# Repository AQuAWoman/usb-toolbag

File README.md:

# usb-toolbag
A versatile USB test kit based around the RP2040 chipset. Includes a pad for 8 bit ONFI standard chips.

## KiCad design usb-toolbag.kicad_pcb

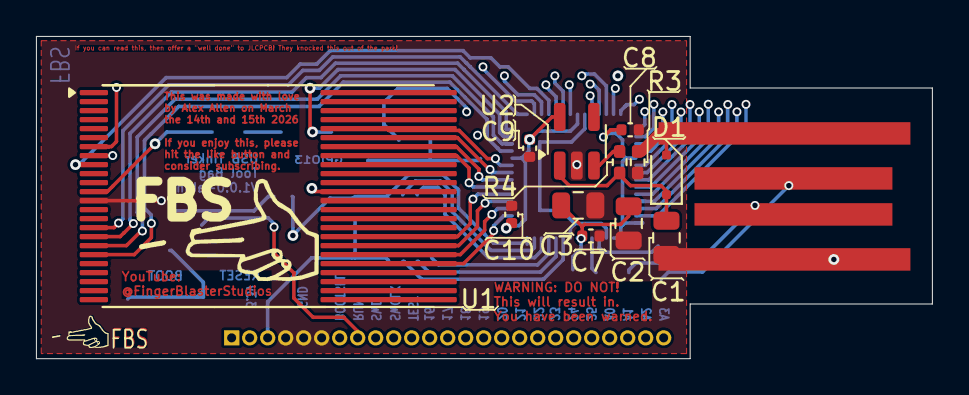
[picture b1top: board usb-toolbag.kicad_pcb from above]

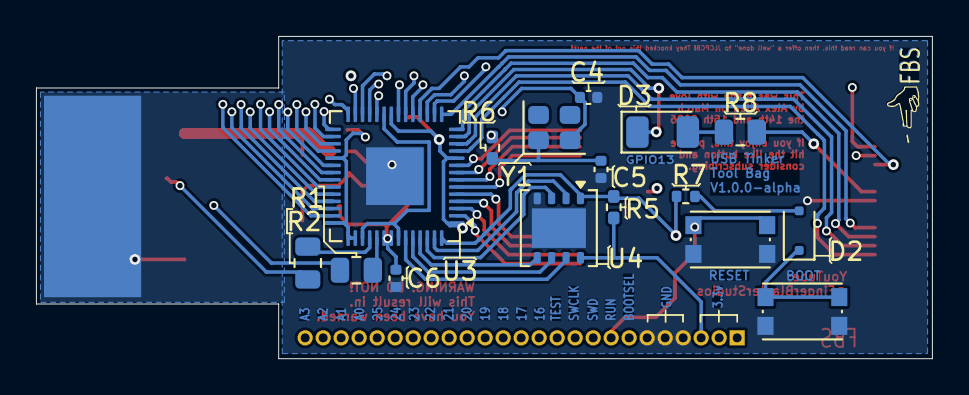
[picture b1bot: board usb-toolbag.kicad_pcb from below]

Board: 4 copper layers, 49.8 x 17.9 mm, 32 parts (16 on the bottom side), 56 nets.

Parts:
C1, C2, C3: 10uF; C_0805_2012Metric
C4, C5: 22pF; C_0402_1005Metric
C6, C7, C8, C9, C10: 0.1uF; C_0402_1005Metric
D1: PMEG2020AEA; D_SOD-323F
D2: 1N4148; D_SOD-323F
D3: LED; LED_1206_3216Metric
J1: USB_A; USB_A_PCB
J2: Conn_01x25_Pin; PinHeader_1x25_P1.00mm_Vertical
LOGO_SILK: LOGO_SILK; fbs_3.5x2mm_silk
LOGO_SILK_LARGE: LOGO_SILK_LARGE; fbs
R1, R2: 22Ω; R_0805_2012Metric
R3, R4, R5: 10kΩ; R_0402_1005Metric_Pad0.72x0.64mm_HandSolder
R6: 1kΩ; R_0402_1005Metric_Pad0.72x0.64mm_HandSolder
R7: 1kΩ; R_0402_1005Metric
R8: 150Ω; R_0805_2012Metric
SW1, SW2: KMR2; SW_Push_1P1T_NO_CK_KMR2
U1: 29F32G08-TSOP48; TSOP-I-48_18.4x12mm_P0.5mm_copy
U2: RT9080-3.3; SOT-23-5_HandSoldering
U3: RP2040; QFN-56-1EP_7x7mm_P0.4mm_EP3.2x3.2mm
U4: 8MB QSPI; WSON-8-1EP_4x4mm_P0.8mm_EP2.2x3mm
Y1: 12MHz; Crystal_SMD_2520-4Pin_2.5x2.0mm

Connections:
/ALE: U1.17 (ALE), U3.14 (GPIO11)
/CLE: U1.16 (CLE), U3.15 (GPIO12)
/CLK: U1.18 (CLK), U3.12 (GPIO9)
/EN: R4.1, U2.3 (EN)
/GPIO16: J2.12, U3.27 (GPIO16)
/GPIO17: J2.13, U3.28 (GPIO17)
/GPIO18: J2.14, U3.29 (GPIO18)
/GPIO19: J2.15, U3.30 (GPIO19)
/GPIO20: J2.16, U3.31 (GPIO20)
/GPIO21: J2.17, U3.32 (GPIO21)
/GPIO22: J2.18, U3.34 (GPIO22)
/GPIO23: J2.19, U3.35 (GPIO23)
/GPIO24: J2.20, U3.36 (GPIO24)
/GPIO25: J2.21, U3.37 (GPIO25)
/GPIO26/A0: J2.22, U3.38 (GPIO26_ADC0)
/GPIO27/A1: J2.23, U3.39 (GPIO27_ADC1)
/GPIO28/A2: J2.24, U3.40 (GPIO28_ADC2)
/GPIO29/A3: J2.25, U3.41 (GPIO29_ADC3)
/LED: D3.1 (K), U3.13 (GPIO10)
/QSPI_CS: J2.7, R5.1, R7.1, U3.56 (QSPI_SS), U4.1 (~CS)
/QSPI_DATA[0]: U3.53 (QSPI_SD0), U4.5 (SI/IO0)
/QSPI_DATA[1]: U3.55 (QSPI_SD1), U4.2 (SO/IO1)
/QSPI_DATA[2]: U3.54 (QSPI_SD2), U4.3 (~WP/IO2)
/QSPI_DATA[3]: U3.51 (QSPI_SD3), U4.7 (~HOLD/~RESET/IO3)
/QSPI_SCK: U3.52 (QSPI_SCLK), U4.6 (SCLK)
/RUN: J2.8, SW1.1, U3.26 (RUN)
/R/_B: U1.7 (R/_B), U3.16 (GPIO13)
/SWCLK: J2.10, U3.24 (SWCLK)
/SWD: J2.9, U3.25 (SWD)
/TESTEN: J2.11, U3.19 (TESTEN)
/VHI: C1.1, D1.1 (K), R4.2, U2.1 (IN)
/W/_R: U1.8 (W/_R), U3.17 (GPIO14)
/_CE: U1.9 (CE), U3.18 (GPIO15)
/_WP: U1.19 (WP), U3.11 (GPIO8)
GND: C1.2, C2.2, C3.2, C4.1, C5.1, C6.2, C7.2, C8.2, C9.2, C10.2, J1.4 (GND), J1.5 (Shield), J2.4, J2.5, J2.6, R3.1, SW1.2, SW2.2, U1.13 (GND), U1.36 (GND), U2.2 (GND), U3.57 (GND), U4.4 (VSS), U4.9 (PAD)
unnamed: C5.2, R6.1, Y1.1
unnamed: D2.2 (A), R7.2
unnamed: D2.1 (K), SW2.1
unnamed: D3.2 (A), R8.2
unnamed: J1.3 (D+), R1.1
unnamed: J1.2 (D-), R2.1
unnamed: U1.29 (DQ0), U3.2 (GPIO0)
unnamed: U1.30 (DQ1), U3.3 (GPIO1)
unnamed: U1.31 (DQ2), U3.4 (GPIO2)
unnamed: U1.32 (DQ3), U3.5 (GPIO3)
unnamed: U1.41 (DQ4), U3.6 (GPIO4)
unnamed: U1.42 (DQ5), U3.7 (GPIO5)
unnamed: U1.43 (DQ6), U3.8 (GPIO6)
unnamed: U1.44 (DQ7), U3.9 (GPIO7)
unnamed: R2.2, U3.46 (USB_DM)
unnamed: R1.2, U3.47 (USB_DP)
unnamed: U3.23 (DVDD), U3.45 (VREG_VOUT), U3.50 (DVDD)
unnamed: C4.2, U3.20 (XIN), Y1.2
unnamed: R6.2, U3.21 (XOUT)
VBUS: D1.2 (A), J1.1 (VBUS), R3.2
VCC: C2.1, C3.1, C6.1, C7.1, C8.1, C9.1, C10.1, J2.1, J2.2, J2.3, R5.2, R8.1, U1.12 (VCC), U1.37 (VCC), U2.5 (OUT), U3.1 (IOVDD), U3.10 (IOVDD), U3.22 (IOVDD), U3.33 (IOVDD), U3.42 (IOVDD), U3.43 (ADC_AVDD), U3.44 (VREG_IN), U3.48 (USB_VDD), U3.49 (IOVDD), U4.8 (VCC)

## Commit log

2026-03-15 Update LICENSE
2026-03-15 Added version 1.0 board files. Fabrication needed before software can be written.
2026-03-15 Hopefully got rid of lock files. Oops.
2026-03-15 maybe fr this time?
2026-03-15 I really should sort out my .gitignore first thing...
2026-03-15 Because it's something I always forget...
2026-03-15 Refilled the main copper sections
2026-03-16 Update schematic
    Tweaked and cleaned up schematic.
2026-03-17 Updated to kicad 9.0.8, cleaned up some traces, fixed symbols and footprints, 3D model view working now.
2026-03-17 Cleaned up more traces
2026-03-17 more cleanup
2026-03-17 I seriously can't help myself...an artist is never done tweaking things...
2026-03-17 something something overworking myself...
2026-03-17 Update renders
2026-03-17 made silk screen pretty
2026-03-17 Updated renders again
2026-03-17 didn't even get them all...
2026-03-17 Sigh...another render update
